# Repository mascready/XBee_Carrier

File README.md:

# XBee_Carrier
A carrier board for XBee 3 to connect to OEM AgGPS

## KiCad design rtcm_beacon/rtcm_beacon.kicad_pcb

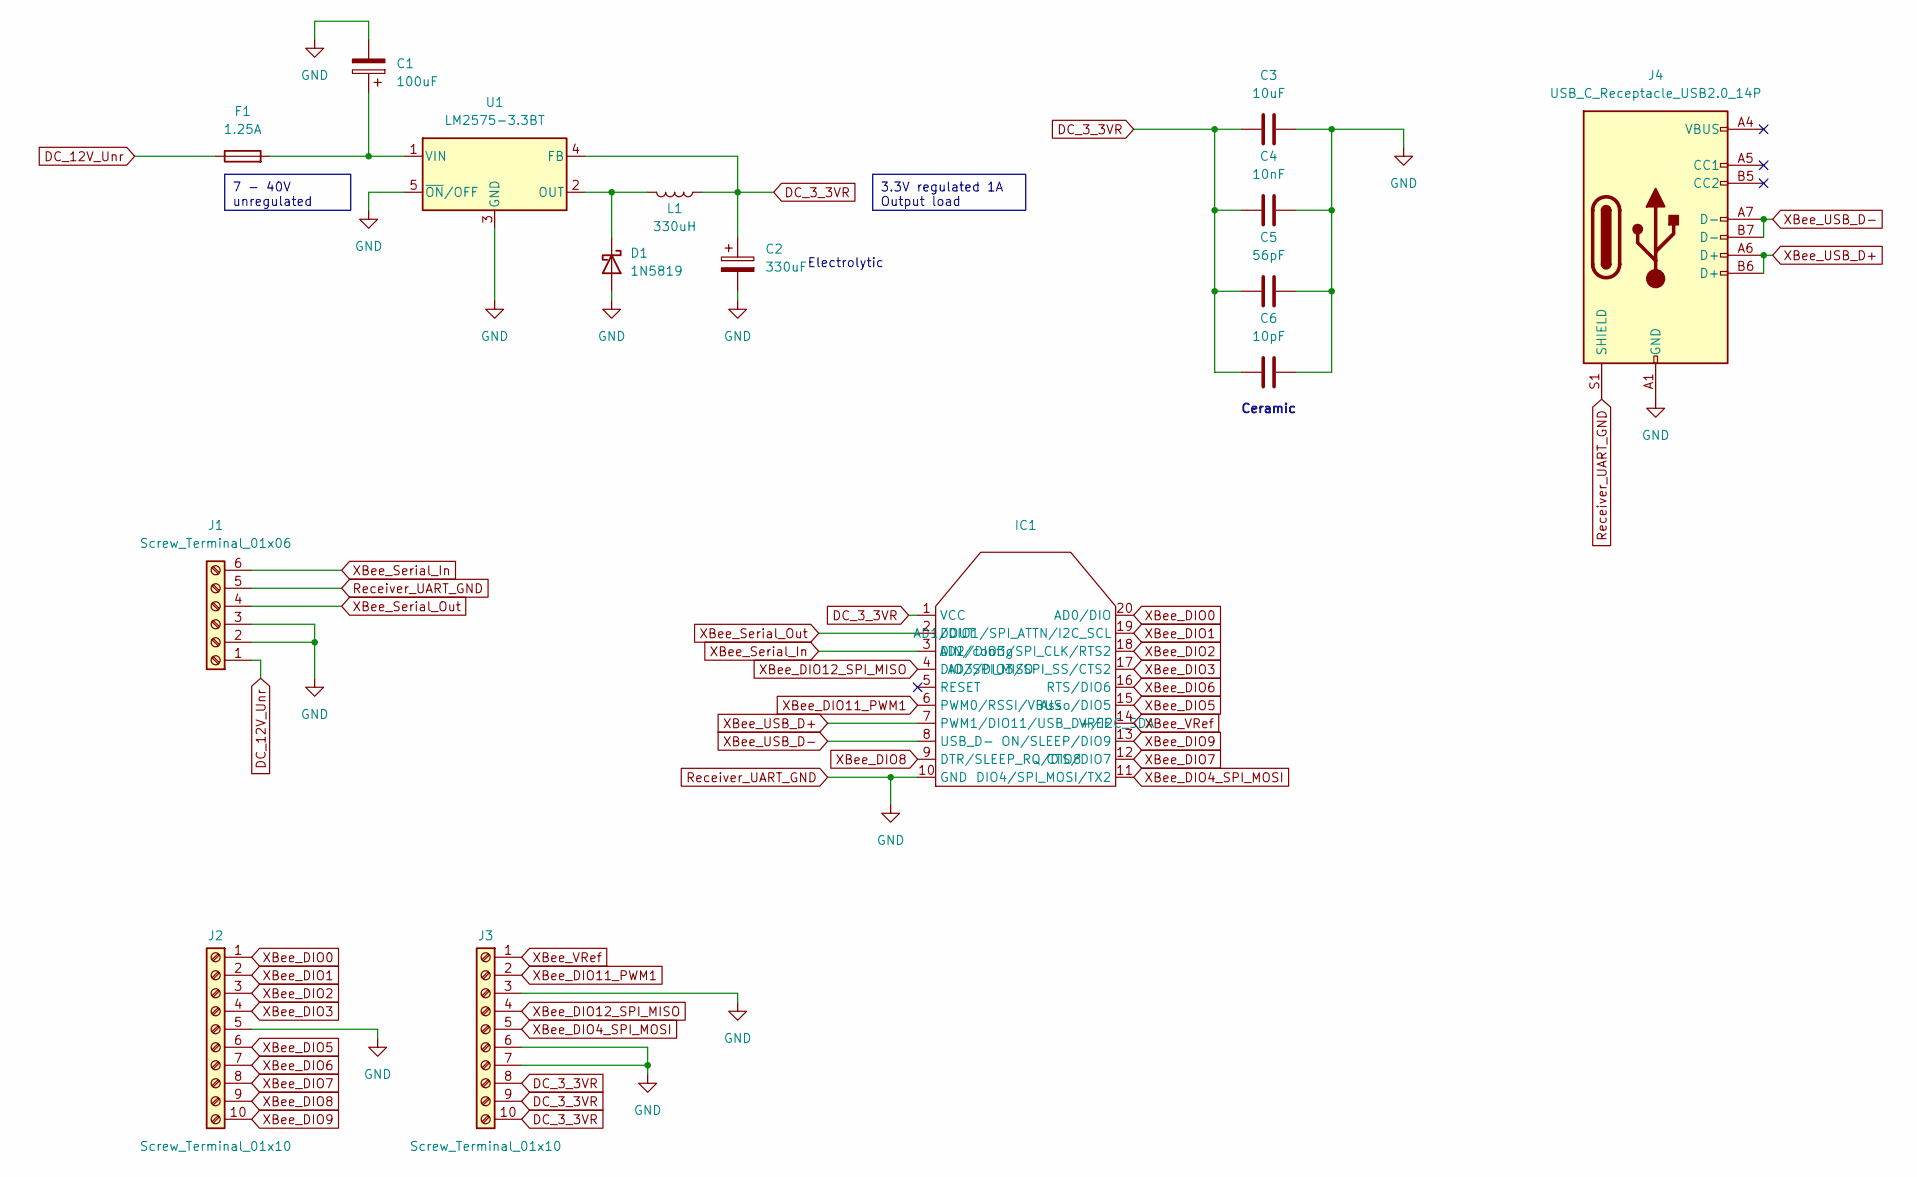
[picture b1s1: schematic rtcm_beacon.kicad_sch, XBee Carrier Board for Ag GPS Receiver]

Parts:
C1: 100uF; CP_Elec_10x12.5
C2: 330uF; CP_Elec_10x12.5
C3: 10uF; C_0603_1608Metric_Pad1.08x0.95mm_HandSolder
C4: 10nF; C_0603_1608Metric_Pad1.08x0.95mm_HandSolder
C5: 56pF; C_0603_1608Metric_Pad1.08x0.95mm_HandSolder
C6: 10pF; C_0603_1608Metric_Pad1.08x0.95mm_HandSolder
D1: 1N5819; D_DO-41_SOD81_P10.16mm_Horizontal
F1: 1.25A; 01530007Z
IC1: Xbee 3
J1: Screw_Terminal_01x06; PhoenixContact_SPT_1.5_6-H-3.5_1x06_P3.5mm_Horizontal
J2, J3: Screw_Terminal_01x10; PinHeader_1x10_P2.00mm_Vertical
J4: USB_C_Receptacle_USB2.0_14P; USB_C_Receptacle_Amphenol_12401548E4-2A_CircularHoles
L1: 330uH; L_Bourns_SRR1208_12.7x12.7mm
U1: LM2575-3.3BT; TO-220-5_Horizontal_TabDown

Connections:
DC_3_3VR: C2.1, C3.1, C4.2, C5.1, C6.1, IC1.1 (VCC), J3.8, J3.9, J3.10, L1.1, U1.4 (FB)
DC_12V_Unr: F1.1, J1.1
unnamed: D1.1 (K), L1.2, U1.2 (OUT)
unnamed: C1.1, F1.2, U1.1 (VIN)
Receiver_UART_GND: C1.2, C2.2, C3.2, C4.1, C5.2, C6.2, D1.2 (A), IC1.10 (GND), J1.2, J1.3, J1.5, J2.5, J3.3, J3.6, J3.7, J4.A1 (GND), J4.A12 (GND), J4.B1 (GND), J4.B12 (GND), J4.S1 (SHIELD), U1.3 (GND), U1.5 (~ON/OFF)
XBee_DIO0: IC1.20 (AD0/DIO), J2.1
XBee_DIO1: IC1.19 (AD1/DIO1/SPI_ATTN/I2C_SCL), J2.2
XBee_DIO2: IC1.18 (AD2/DIO3/SPI_CLK/RTS2), J2.3
XBee_DIO3: IC1.17 (AD3/DIO3/SPI_SS/CTS2), J2.4
XBee_DIO4_SPI_MOSI: IC1.11 (DIO4/SPI_MOSI/TX2), J3.5
XBee_DIO5: IC1.15 (Asso/DIO5), J2.6
XBee_DIO6: IC1.16 (RTS/DIO6), J2.7
XBee_DIO7: IC1.12 (CTS/DIO7), J2.8
XBee_DIO8: IC1.9 (DTR/SLEEP_RQ/DIO8), J2.9
XBee_DIO9: IC1.13 (ON/SLEEP/DIO9), J2.10
XBee_DIO11_PWM1: IC1.6 (PWM0/RSSI/VBUS), J3.2
XBee_DIO12_SPI_MISO: IC1.4 (DIO/SPI_MISO), J3.4
XBee_Serial_In: IC1.3 (DIN/config), J1.6
XBee_Serial_Out: IC1.2 (DOUT), J1.4
XBee_USB_D+: IC1.7 (PWM1/DIO11/USB_D+/I2C_SDA), J4.A6 (D+), J4.B6 (D+)
XBee_USB_D-: IC1.8 (USB_D-), J4.A7 (D-), J4.B7 (D-)
XBee_VRef: IC1.14 (VREF), J3.1

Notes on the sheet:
3.3V regulated 1A Output load
7 - 40V unregulated
Ceramic
Electrolytic

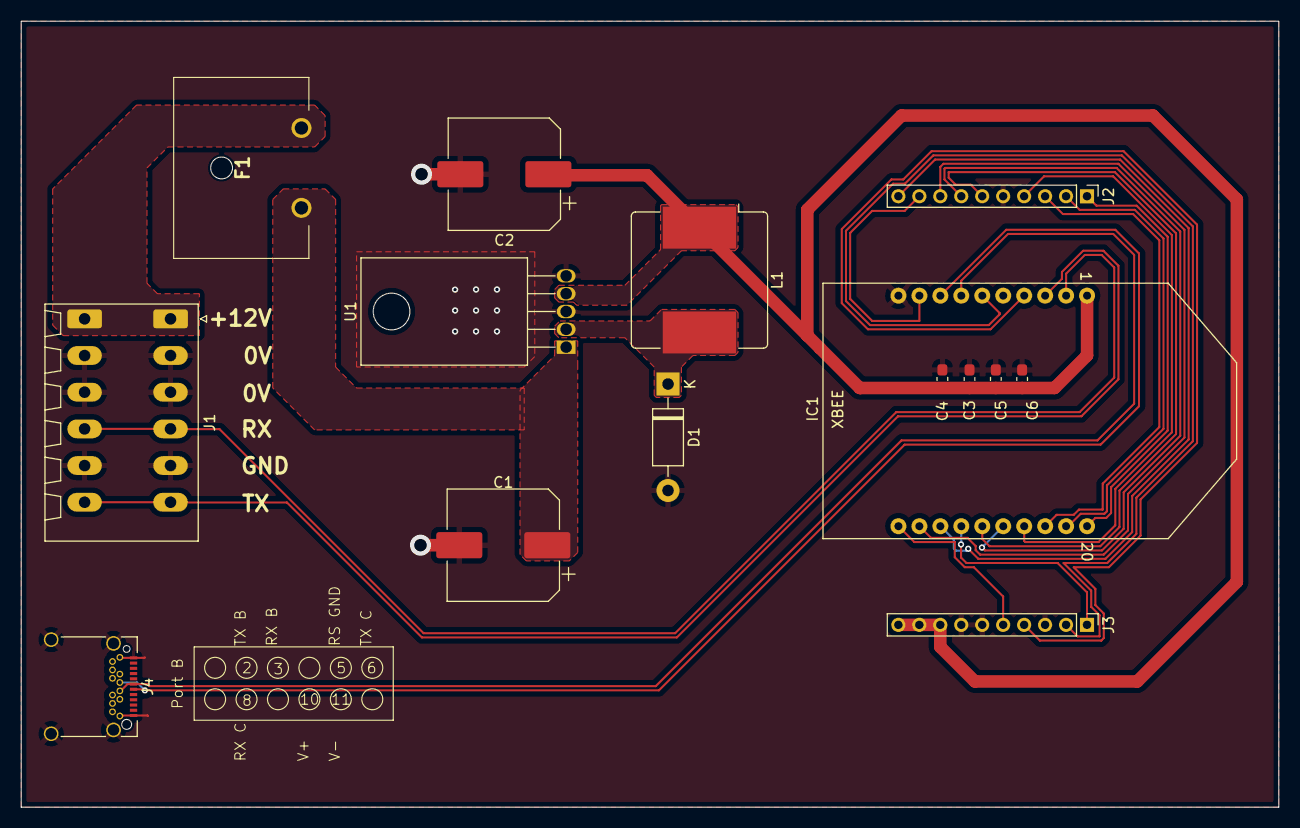
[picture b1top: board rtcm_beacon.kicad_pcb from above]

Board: 2 copper layers, 120.0 x 75.0 mm, 15 parts (0 on the bottom side), 22 nets.

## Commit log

2024-12-31 Initial release
